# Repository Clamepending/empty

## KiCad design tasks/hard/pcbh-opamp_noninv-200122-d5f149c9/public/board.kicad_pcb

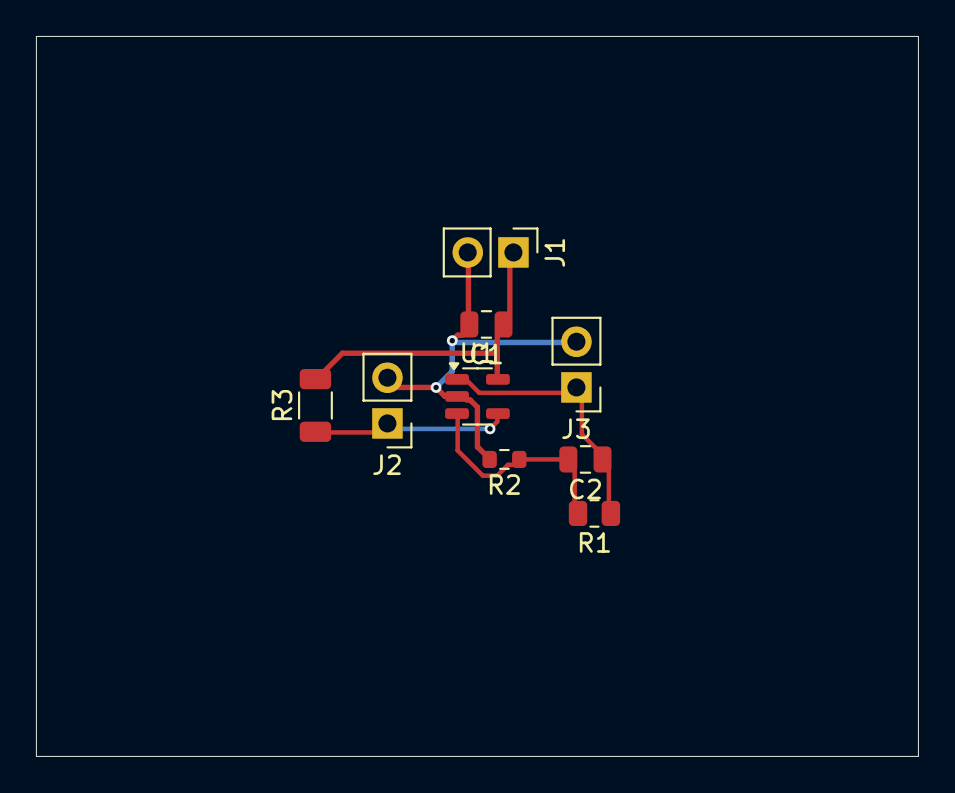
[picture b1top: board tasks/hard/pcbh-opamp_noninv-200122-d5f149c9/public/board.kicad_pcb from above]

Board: 2 copper layers, 49.0 x 40.0 mm, 9 parts (0 on the bottom side), 5 nets.

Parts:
C1: 100n; C_0805_2012Metric
C2: 270p; C_0805_2012Metric
J1, J2, J3: PinHeader_1x02_P2.54mm_Vertical
R1: 110k; R_0805_2012Metric
R2: 5.76k; R_0603_1608Metric
R3: 470k; R_1206_3216Metric
U1: SOT-23-5

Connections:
FB: C2.2, R1.2, R2.1, U1.3
GND: C1.2, J1.2, J2.2, J3.2, R2.2, U1.2
IN: J2.1, R3.1, U1.4
OUT: C2.1, J3.1, R1.1, U1.1
VCC: C1.1, J1.1, R3.2, U1.5

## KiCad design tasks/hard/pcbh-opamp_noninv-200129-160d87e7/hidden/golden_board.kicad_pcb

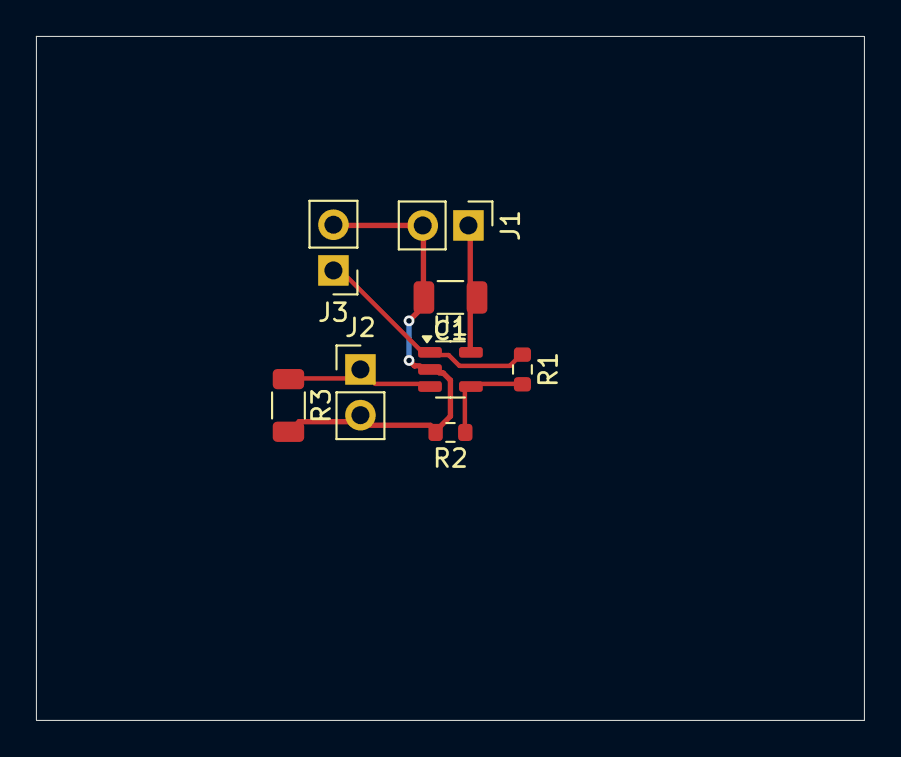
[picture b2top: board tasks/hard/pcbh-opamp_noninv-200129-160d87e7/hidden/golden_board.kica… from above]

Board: 2 copper layers, 46.0 x 38.0 mm, 8 parts (0 on the bottom side), 5 nets.

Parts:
C1: 100n; C_1206_3216Metric
J1, J2, J3: PinHeader_1x02_P2.54mm_Vertical
R1: 64.9k; R_0603_1608Metric
R2: 7.15k; R_0603_1608Metric
R3: 220k; R_1206_3216Metric
U1: SOT-23-5

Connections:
FB: R1.2, R2.1, U1.4
GND: C1.2, J1.2, J2.2, J3.2, R2.2, R3.2, U1.2
IN: J2.1, R3.1, U1.3
OUT: J3.1, R1.1, U1.1
VCC: C1.1, J1.1, U1.5

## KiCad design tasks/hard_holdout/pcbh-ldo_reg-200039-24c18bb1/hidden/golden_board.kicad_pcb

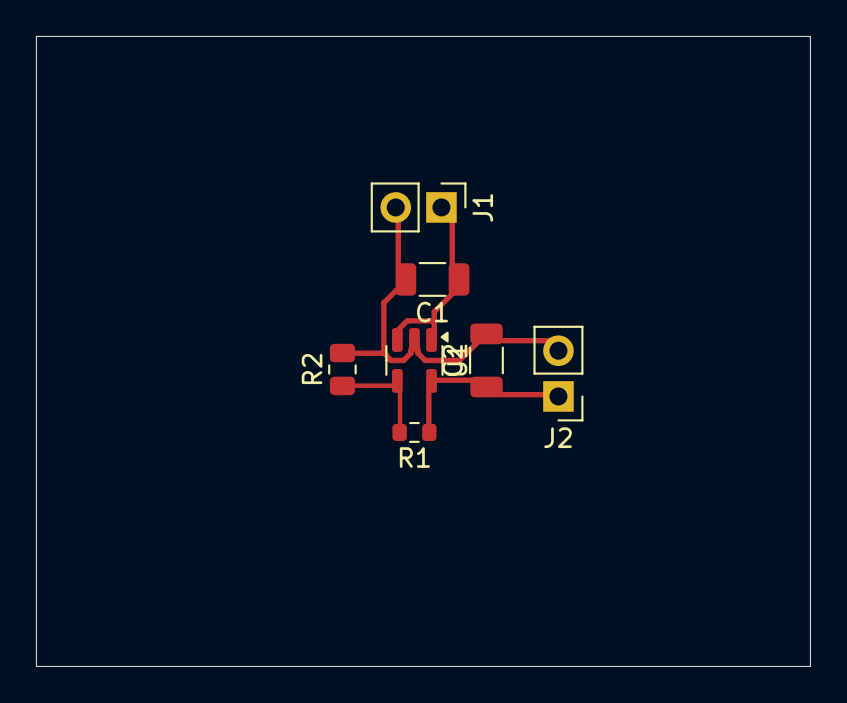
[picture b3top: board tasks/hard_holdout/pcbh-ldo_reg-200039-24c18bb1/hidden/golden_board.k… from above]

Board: 2 copper layers, 43.0 x 35.0 mm, 7 parts (0 on the bottom side), 4 nets.

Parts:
C1: 4.7u; C_1206_3216Metric
C2: 10u; C_1206_3216Metric
J1, J2: PinHeader_1x02_P2.54mm_Vertical
R1: 12.4k; R_0603_1608Metric
R2: 10k; R_0805_2012Metric
U1: SOT-23-5

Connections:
+1V8: C2.1, J2.1, R1.1, U1.5
FB: R1.2, R2.1, U1.4
GND: C1.2, C2.2, J1.2, J2.2, R2.2, U1.2
VIN: C1.1, J1.1, U1.1, U1.3

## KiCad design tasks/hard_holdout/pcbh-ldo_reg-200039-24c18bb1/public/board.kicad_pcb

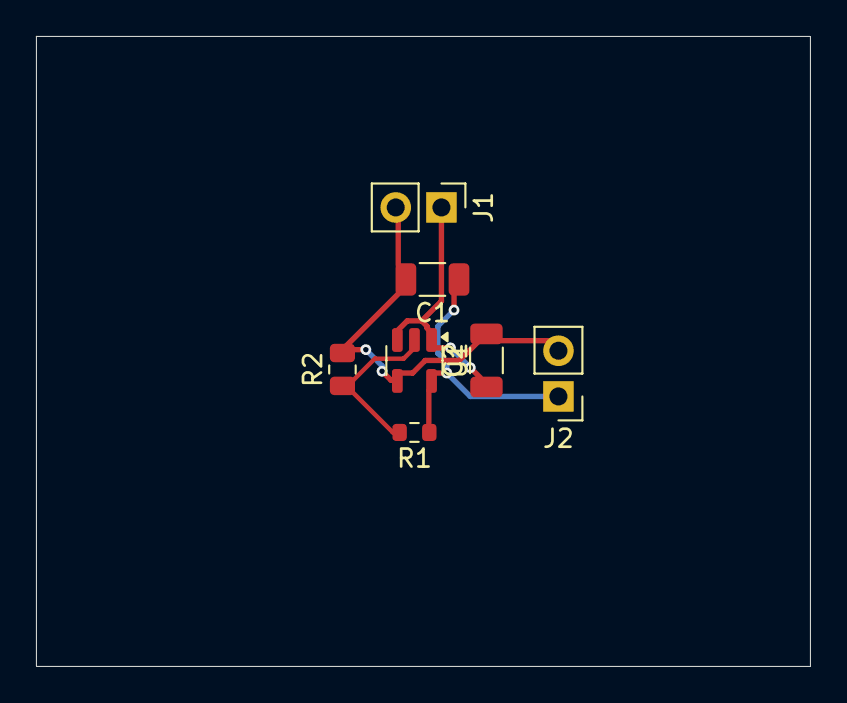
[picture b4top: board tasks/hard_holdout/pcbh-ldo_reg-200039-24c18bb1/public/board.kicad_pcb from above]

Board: 2 copper layers, 43.0 x 35.0 mm, 7 parts (0 on the bottom side), 4 nets.

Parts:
C1: 4.7u; C_1206_3216Metric
C2: 10u; C_1206_3216Metric
J1, J2: PinHeader_1x02_P2.54mm_Vertical
R1: 12.4k; R_0603_1608Metric
R2: 10k; R_0805_2012Metric
U1: SOT-23-5

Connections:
+1V8: C1.1, J2.1, R1.1, U1.5
FB: R1.2, R2.1, U1.2
GND: C1.2, C2.2, J1.2, J2.2, R2.2, U1.4
VIN: C2.1, J1.1, U1.1, U1.3
